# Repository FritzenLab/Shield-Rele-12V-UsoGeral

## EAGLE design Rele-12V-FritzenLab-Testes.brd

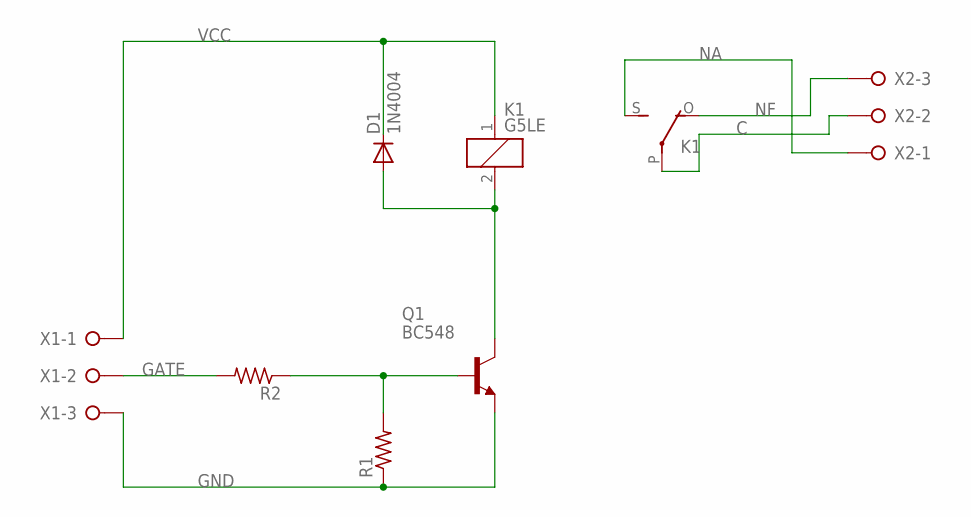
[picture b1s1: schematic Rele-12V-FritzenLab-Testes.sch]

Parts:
D1: 1N4004; DO41-10
K1: G5LE
Q1: BC548; TO92-EBC
R1, R2: R-US_0207/10; 0207/10
X1, X2: W237-3E

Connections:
C: K1.P, X2.2
GATE: R2.2, X1.2
GND: Q1.E, R1.1, X1.3
unnamed: Q1.B, R1.2, R2.1
unnamed: D1.A, K1.2, Q1.C
NA: K1.S, X2.1
NF: K1.O, X2.3
VCC: D1.C, K1.1, X1.1

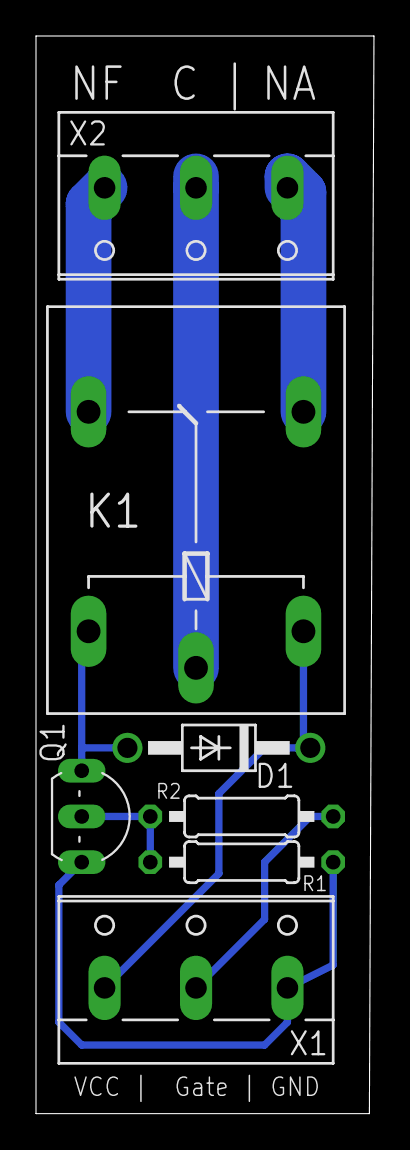
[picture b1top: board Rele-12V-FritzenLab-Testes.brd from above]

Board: 2 copper layers, 18.8 x 59.9 mm, 7 parts (0 on the bottom side), 8 nets.

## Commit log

2018-03-10 added PNG image
